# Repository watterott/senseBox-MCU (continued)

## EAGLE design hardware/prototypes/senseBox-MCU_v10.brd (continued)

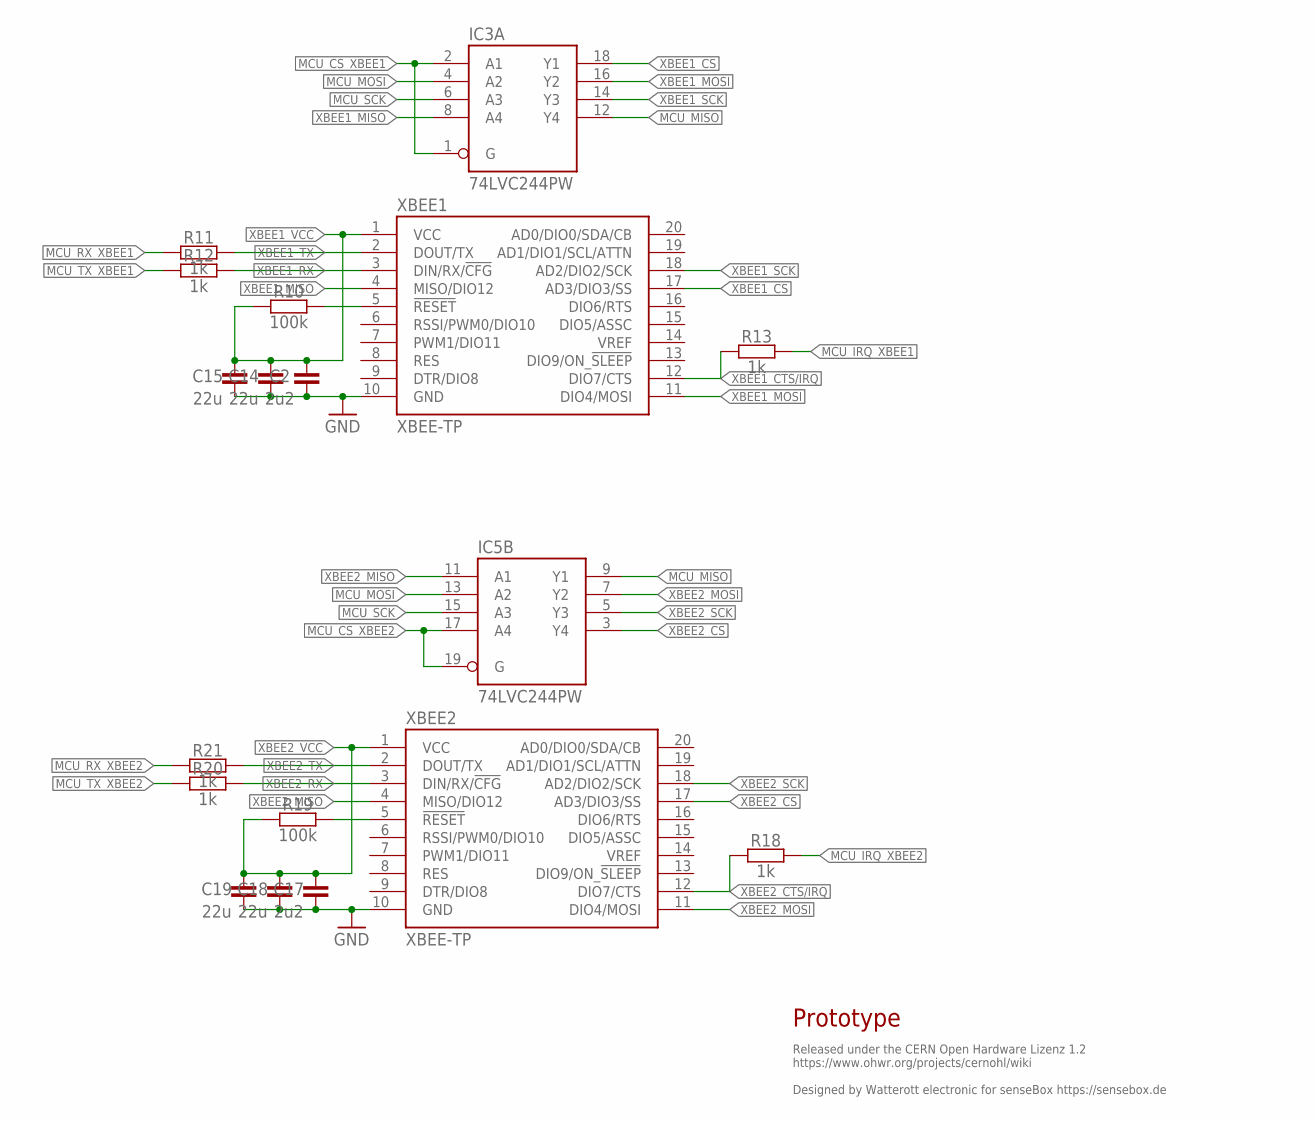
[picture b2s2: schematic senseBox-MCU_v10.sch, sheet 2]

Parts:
C2, C17: 2u2; C0402
C14, C15, C18, C19: 22u; C0805
IC3, IC5: 74LVC244PW; TSSOP20
R10, R19: 100k; C0402
R11, R12, R13, R18, R20, R21: 1k; C0402
XBEE1, XBEE2: XBEE-TP; XBEE_TP

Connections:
GND: C2.1, C14.1, C15.1, C17.1, C18.1, C19.1, XBEE1.10 (GND), XBEE2.10 (GND); also elsewhere on the board
MCU_CS_XBEE1: IC3.1 (G), IC3.2 (A1); also elsewhere on the board
MCU_CS_XBEE2: IC5.17 (A4), IC5.19 (G); also elsewhere on the board
MCU_IRQ_XBEE1: R13.2; also elsewhere on the board
MCU_IRQ_XBEE2: R18.2; also elsewhere on the board
MCU_MISO: IC3.12 (Y4), IC5.9 (Y1); also elsewhere on the board
MCU_MOSI: IC3.4 (A2), IC5.13 (A2); also elsewhere on the board
MCU_RX_XBEE1: R11.1; also elsewhere on the board
MCU_RX_XBEE2: R21.1; also elsewhere on the board
MCU_SCK: IC3.6 (A3), IC5.15 (A3); also elsewhere on the board
MCU_TX_XBEE1: R12.1; also elsewhere on the board
MCU_TX_XBEE2: R20.1; also elsewhere on the board
unnamed: R19.2, XBEE2.5 (!RESET!)
unnamed: R10.2, XBEE1.5 (!RESET!)
XBEE1_CS: IC3.18 (Y1), XBEE1.17 (AD3/DIO3/SS)
XBEE1_CTS/IRQ: R13.1, XBEE1.12 (DIO7/CTS)
XBEE1_MISO: IC3.8 (A4), XBEE1.4 (MISO/DIO12)
XBEE1_MOSI: IC3.16 (Y2), XBEE1.11 (DIO4/MOSI)
XBEE1_RX: R12.2, XBEE1.3 (DIN/RX/!CFG!)
XBEE1_SCK: IC3.14 (Y3), XBEE1.18 (AD2/DIO2/SCK)
XBEE1_TX: R11.2, XBEE1.2 (DOUT/TX)
XBEE1_VCC: C2.2, C14.2, C15.2, R10.1, XBEE1.1 (VCC); also elsewhere on the board
XBEE2_CS: IC5.3 (Y4), XBEE2.17 (AD3/DIO3/SS)
XBEE2_CTS/IRQ: R18.1, XBEE2.12 (DIO7/CTS)
XBEE2_MISO: IC5.11 (A1), XBEE2.4 (MISO/DIO12)
XBEE2_MOSI: IC5.7 (Y2), XBEE2.11 (DIO4/MOSI)
XBEE2_RX: R20.2, XBEE2.3 (DIN/RX/!CFG!)
XBEE2_SCK: IC5.5 (Y3), XBEE2.18 (AD2/DIO2/SCK)
XBEE2_TX: R21.2, XBEE2.2 (DOUT/TX)
XBEE2_VCC: C17.2, C18.2, C19.2, R19.1, XBEE2.1 (VCC); also elsewhere on the board

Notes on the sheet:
Released under the CERN Open Hardware Lizenz 1.2 https://www.ohwr.org/projects/cernohl/wiki Designed by Watterott electronic for senseBox https://sensebox.de
Prototype

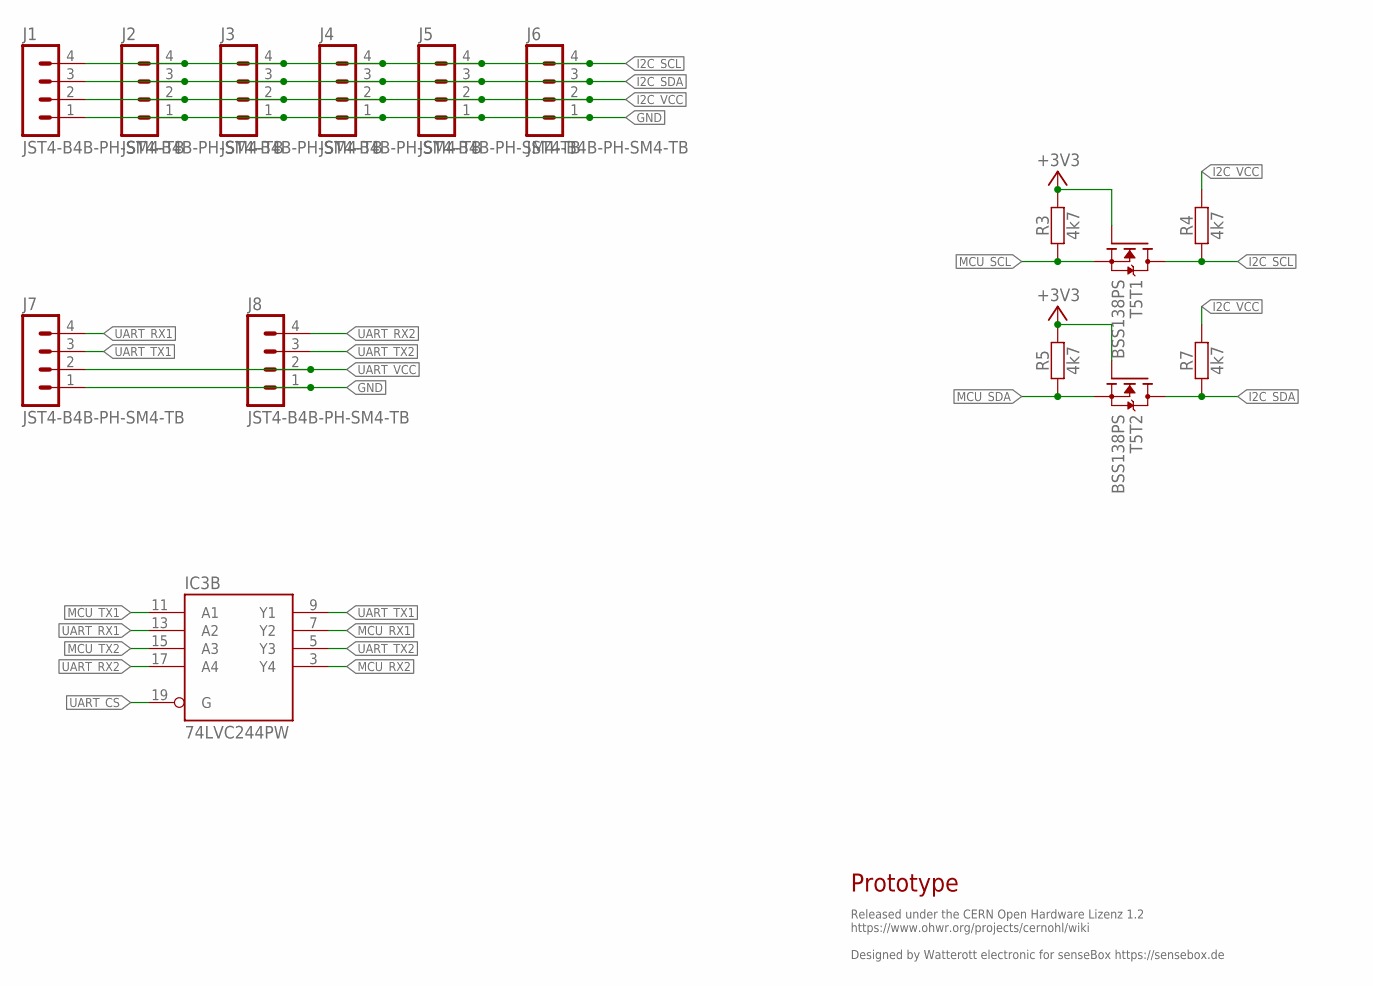
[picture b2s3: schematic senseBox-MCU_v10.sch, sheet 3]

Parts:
IC3: 74LVC244PW; TSSOP20
J1, J2, J3, J4, J5, J6, J7, J8: JST4-B4B-PH-SM4-TB; JST_B4B-PH-SM4-TB
R3, R4, R5, R7: 4k7; C0402
T5: BSS138PS; SOT363

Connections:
+3V3: R3.2, R5.2, T5.2 (G), T5.5 (G); also elsewhere on the board
GND: J1.1, J2.1, J3.1, J4.1, J5.1, J6.1, J7.1, J8.1; also elsewhere on the board
I2C_SCL: J1.4, J2.4, J3.4, J4.4, J5.4, J6.4, R4.1, T5.6 (D)
I2C_SDA: J1.3, J2.3, J3.3, J4.3, J5.3, J6.3, R7.1, T5.3 (D)
I2C_VCC: J1.2, J2.2, J3.2, J4.2, J5.2, J6.2, R4.2, R7.2; also elsewhere on the board
MCU_RX1: IC3.7 (Y2); also elsewhere on the board
MCU_RX2: IC3.3 (Y4); also elsewhere on the board
MCU_SCL: R3.1, T5.1 (S); also elsewhere on the board
MCU_SDA: R5.1, T5.4 (S); also elsewhere on the board
MCU_TX1: IC3.11 (A1); also elsewhere on the board
MCU_TX2: IC3.15 (A3); also elsewhere on the board
UART_CS: IC3.19 (G); also elsewhere on the board
UART_RX1: IC3.13 (A2), J7.4
UART_RX2: IC3.17 (A4), J8.4
UART_TX1: IC3.9 (Y1), J7.3
UART_TX2: IC3.5 (Y3), J8.3
UART_VCC: J7.2, J8.2; also elsewhere on the board

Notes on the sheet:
Released under the CERN Open Hardware Lizenz 1.2 https://www.ohwr.org/projects/cernohl/wiki Designed by Watterott electronic for senseBox https://sensebox.de
Prototype

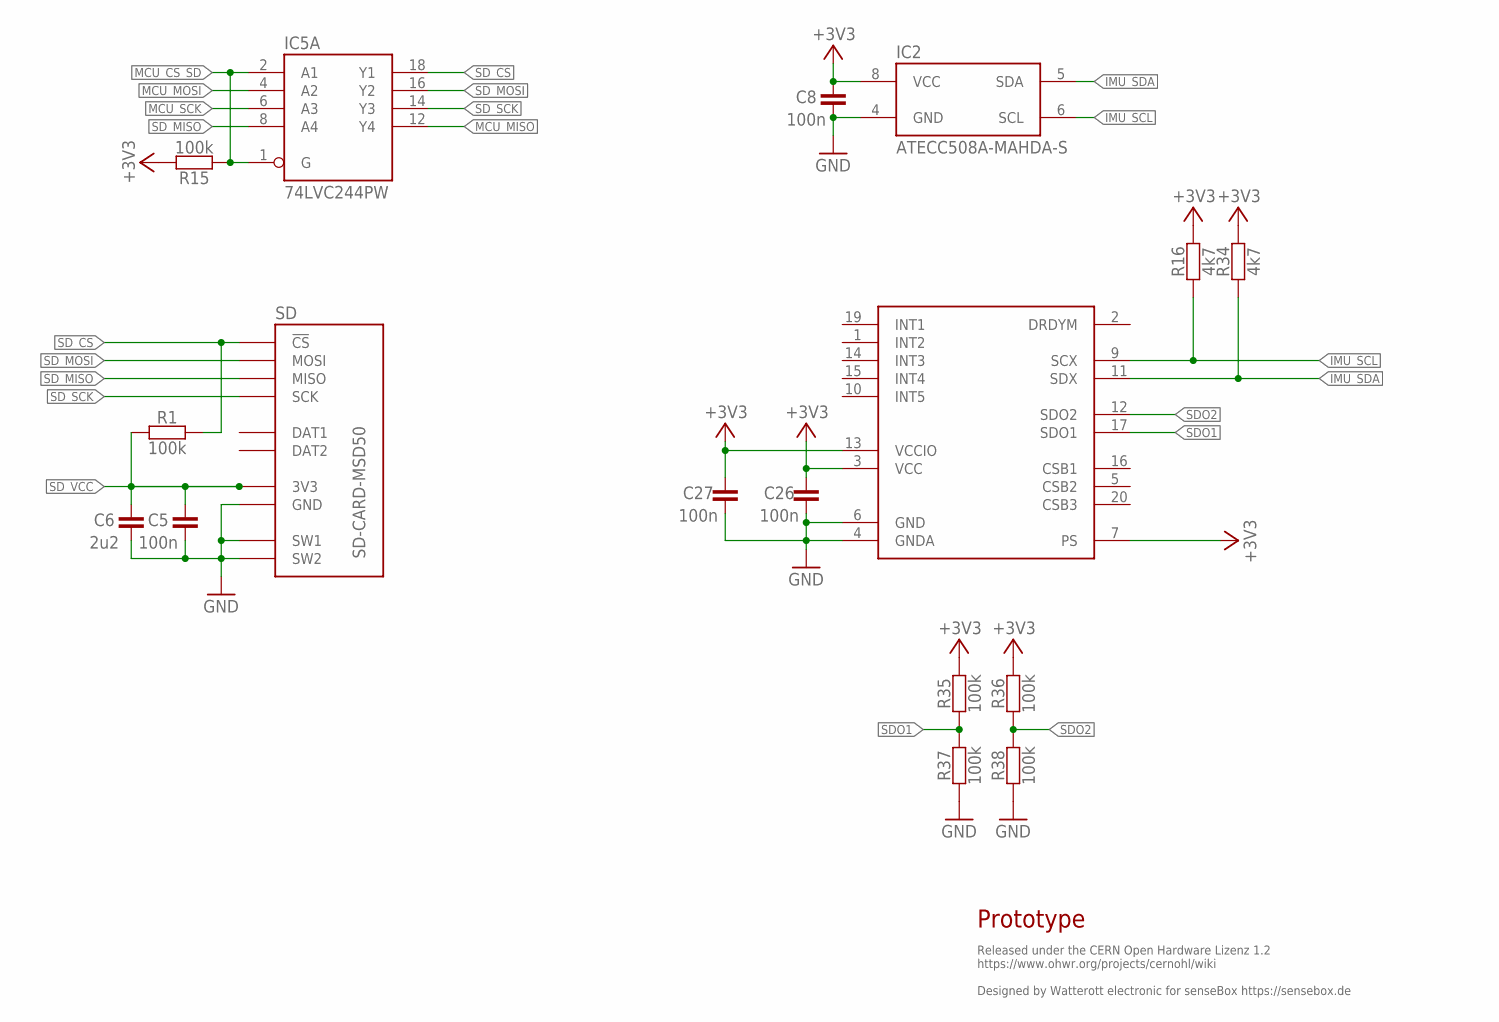
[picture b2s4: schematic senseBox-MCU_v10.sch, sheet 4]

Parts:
C5, C8, C26, C27: 100n; C0402
C6: 2u2; C0402
IC2: ATECC508A-MAHDA-S; UDFN8
IC5: 74LVC244PW; TSSOP20
R1, R15, R35, R36, R37, R38: 100k; C0402
R16, R34: 4k7; C0402
SD: SD-CARD-MSD50; SD_5031821853
U1: BMX055

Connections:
+3V3: C8.2, C26.2, C27.2, IC2.8 (VCC), R15.2, R16.2, R34.2, R35.2, R36.2, U1.3 (VCC), U1.7 (PS), U1.13 (VCCIO); also elsewhere on the board
GND: C5.1, C6.1, C8.1, C26.1, C27.1, IC2.4 (GND), R37.1, R38.1, SD.GND, SD.SW1, SD.SW2, U1.4 (GNDA), U1.6 (GND); also elsewhere on the board
IMU_SCL: IC2.6 (SCL), R16.1, U1.9 (SCX); also elsewhere on the board
IMU_SDA: IC2.5 (SDA), R34.1, U1.11 (SDX); also elsewhere on the board
MCU_CS_SD: IC5.1 (G), IC5.2 (A1), R15.1; also elsewhere on the board
MCU_MISO: IC5.12 (Y4); also elsewhere on the board
MCU_MOSI: IC5.4 (A2); also elsewhere on the board
MCU_SCK: IC5.6 (A3); also elsewhere on the board
SDO1: R35.1, R37.2, U1.17 (SDO1)
SDO2: R36.1, R38.2, U1.12 (SDO2)
SD_CS: IC5.18 (Y1), R1.2, SD.CS (!CS)
SD_MISO: IC5.8 (A4), SD.MISO
SD_MOSI: IC5.16 (Y2), SD.MOSI
SD_SCK: IC5.14 (Y3), SD.SCK
SD_VCC: C5.2, C6.2, R1.1, SD.VCC (3V3); also elsewhere on the board

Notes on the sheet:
Released under the CERN Open Hardware Lizenz 1.2 https://www.ohwr.org/projects/cernohl/wiki Designed by Watterott electronic for senseBox https://sensebox.de
Prototype

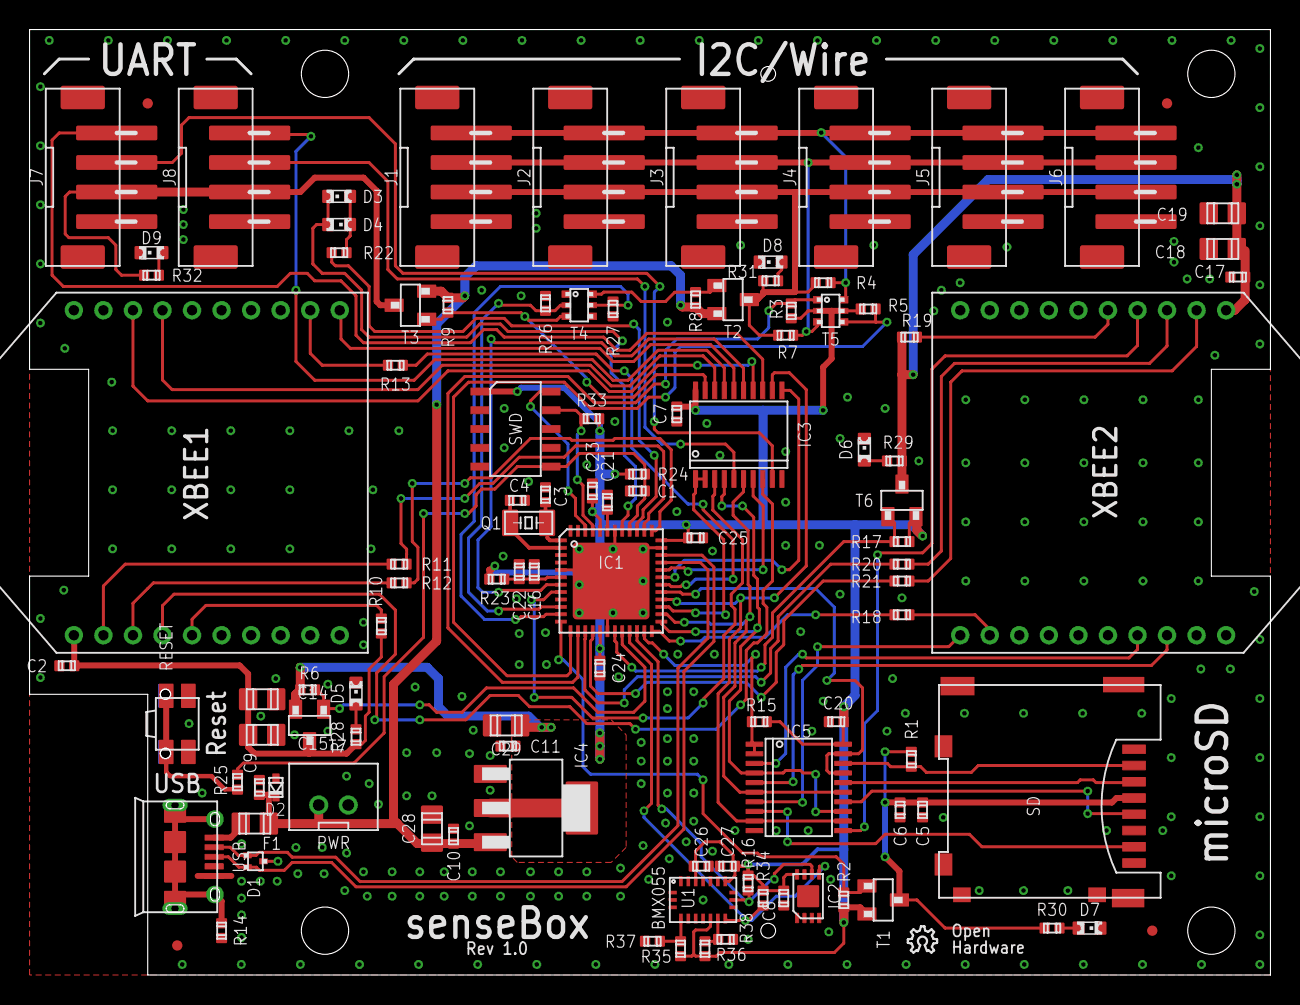
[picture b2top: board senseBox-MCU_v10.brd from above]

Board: 2 copper layers, 84.0 x 64.0 mm, 109 parts (0 on the bottom side), 83 nets.

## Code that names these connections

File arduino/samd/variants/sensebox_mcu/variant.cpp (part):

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 |            |                  |        |                 |   EIC  | ADC |  AC | PTC | DAC | SERCOMx | SERCOMx |  TCCx  |  TCCx  |    COM   | AC/GLCK  |
 |            |                  |        |                 |(EXTINT)|(AIN)|(AIN)|     |     | (x/PAD) | (x/PAD) | (x/WO) | (x/WO) |          |          |
 +------------+------------------+--------+-----------------+--------+-----+-----+-----+-----+---------+---------+--------+--------+----------+----------+
 | 00         | SW               |  PA20  |                 |  *04   |     |     | X08 |     |   5/02  |   3/02  |        |*TCC0/6 | I2S/SCK0 | GCLK_IO4 |
 | 01         | IO1 / REFB       |  PA04  |                 |   04   | *04 |  00 | Y02 |     |         |   0/00  |*TCC0/0 |        |          |          |
 | 02         | IO2              |  PA05  |                 |   05   | *05 |  01 | Y03 |     |         |   0/01  |*TCC0/1 |        |          |          |
 | 03         | IO3              |  PA06  |                 |   06   | *06 |  02 | Y04 |     |         |   0/02  | TCC1/0 |        |          |          |
 | 04         | IO4              |  PA07  |                 |   07   | *07 |  03 | Y05 |     |         |   0/03  | TCC1/1 |        | I2S/SD0  |          |
 | 05         | IO5 / REFA       |  PA03  |                 |   03   |  01 |     | Y01 |     |         |         |        |        |          |          |
 | 06         | IO6 / DAC0       |  PA02  |                 |   02   | *00 |     | Y00 | OUT |         |         |        |        |          |          |
 | 07         | LED red          |  PA27  |                 |   15   |     |     |     |     |         |         |        |        |          | GCLK_IO0 |
 | 08         | LED green        |  PA28  |                 |   08   |     |     |     |     |         |         |        |        |          | GCLK_IO0 |
 +------------+------------------+--------+-----------------+--------+-----+-----+-----+-----+---------+---------+--------+--------+----------+----------+
 */
  { PORTA, 20, PIO_DIGITAL, (PIN_ATTR_DIGITAL                                ), No_ADC_Channel, NOT_ON_PWM, NOT_ON_TIMER, EXTERNAL_INT_4    }, // SW
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 |            |                  |        |                 |   EIC  | ADC |  AC | PTC | DAC | SERCOMx | SERCOMx |  TCCx  |  TCCx  |    COM   | AC/GLCK  |
 |            |                  |        |                 |(EXTINT)|(AIN)|(AIN)|     |     | (x/PAD) | (x/PAD) | (x/WO) | (x/WO) |          |          |
 +------------+------------------+--------+-----------------+--------+-----+-----+-----+-----+---------+---------+--------+--------+----------+----------+
 | 09         | PWR UART         |  PB02  |                 |  *02   | *10 |     | Y08 |     |         |   5/00  |        |        |          |          |
 | 10         | TX1              |  PA22  |                 |  *06   |     |     | X10 |     |   3/00  |   5/00  |* TC4/0 | TCC0/4 |          | GCLK_IO6 |
 | 11         | RX1              |  PA23  |                 |  *07   |     |     | X11 |     |   3/01  |   5/01  |* TC4/1 | TCC0/5 | USB/SOF  | GCLK_IO7 |
 | 12         | TX2              |  PB08  |                 |   08   |  02 |     | Y14 |     |         |   4/00  |  TC4/0 |        |          |          |
 | 13         | RX2              |  PB09  |                 |  *09   |  03 |     | Y15 |     |         |   4/01  |  TC4/1 |        |          |          |
 +------------+------------------+--------+-----------------+--------------------+-----+-----+---------+---------+--------+--------+----------+----------+
 | 14         | PWR I2C          |  PB11  |                 |  *11   |     |     |     |     |         |   4/03  |* TC5/1 | TCC0/5 | I2S/SCK1 | GCLK_IO5 |
 | 15         | SDA              |  PA08  |                 |   NMI  | *16 |     | X00 |     |  *0/00  |   2/00  | TCC0/0 | TCC1/2 | I2S/SD1  |          |
 | 16         | SCL              |  PA09  |                 |   09   | *17 |     | X01 |     |  *0/01  |   2/01  | TCC0/1 | TCC1/3 | I2S/MCK0 |          |
 +------------+------------------+--------+-----------------+--------------------+-----+-----+---------+---------+--------+--------+----------+----------+
 | 17         | SDA IMU          |  PA12  |                 |   12   |     |     |     |     |  *2/00  |   4/00  | TCC2/0 | TCC0/6 |          | AC/CMP0  |
 | 18         | SCL IMU          |  PA13  |                 |   13   |     |     |     |     |  *2/01  |   4/01  | TCC2/1 | TCC0/7 |          | AC/CMP1  |
 +------------+------------------+--------+-----------------+--------------------+-----+-----+---------+---------+--------+--------+----------+----------+
 | 19         | MOSI             |  PA16  |                 |  *00   |     |     | X04 |     |  *1/00  |   3/00  |*TCC2/0 | TCC0/6 |          | GCLK_IO2 |
 | 20         | SCK              |  PA17  |                 |  *01   |     |     | X05 |     |  *1/01  |   3/01  | TCC2/1 | TCC0/7 |          | GCLK_IO3 |
 | 21         | MISO             |  PA19  |                 |   03   |     |     | X07 |     |  *1/03  |   3/03  |* TC3/1 | TCC0/3 | I2S/SD0  | AC/CMP1  |
 +------------+------------------+--------+-----------------+--------------------+-----+-----+---------+---------+--------+--------+----------+----------+
 */
  { PORTB,  2, PIO_DIGITAL, (PIN_ATTR_DIGITAL                                ), No_ADC_Channel, NOT_ON_PWM, NOT_ON_TIMER, EXTERNAL_INT_NONE }, // PWR UART
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 |            |                  |        |                 |   EIC  | ADC |  AC | PTC | DAC | SERCOMx | SERCOMx |  TCCx  |  TCCx  |    COM   | AC/GLCK  |
 |            |                  |        |                 |(EXTINT)|(AIN)|(AIN)|     |     | (x/PAD) | (x/PAD) | (x/WO) | (x/WO) |          |          |
 +------------+------------------+--------+-----------------+--------+-----+-----+-----+-----+---------+---------+--------+--------+----------+----------+
 | 22         | PWR XB1          |  PB03  |                 |  *03   | *11 |     | Y09 |     |         |   5/01  |        |        |          |          |
 | 23         | CS XB1           |  PA18  |                 |   02   |     |     | X06 |     |   1/02  |   3/02  |  TC3/0 | TCC0/2 |          | AC/CMP0  |
 | 24         | INT XB1          |  PA21  |                 |  *05   |     |     | X09 |     |   5/03  |   3/03  |        |*TCC0/7 | I2S/FS0  | GCLK_IO5 |
 | 25         | RX XB1           |  PB23  |                 |   07   |     |     |     |     |         |  *5/03  |        |        |          | GCLK_IO1 |
 | 26         | TX XB1           |  PB22  |                 |   06   |     |     |     |     |         |  *5/02  |        |        |          | GCLK_IO0 |
 +------------+------------------+--------+-----------------+--------------------+-----+-----+---------+---------+--------+--------+----------+----------+
 | 27         | PWR XB2          |  PB10  |                 |  *10   |     |     |     |     |         |   4/02  |* TC5/0 | TCC0/4 | I2S/MCK1 | GCLK_IO4 |
 | 28         | D28 XB2          |  PA14  |                 |   14   |     |     |     |     |   2/02  |   4/02  |  TC3/0 | TCC0/4 |          | GCLK_IO0 |
 | 29         | D29 XB2          |  PA15  |                 |   15   |     |     |     |     |  *2/03  |   4/03  |  TC3/1 | TCC0/5 |          | GCLK_IO1 |
 | 30         | TX XB2           |  PA10  |                 |   10   | *18 |     | X02 |     |   0/02  |   2/02  |*TCC1/0 | TCC0/2 | I2S/SCK0 | GCLK_IO4 |
 | 31         | RX XB2           |  PA11  |                 |   11   | *19 |     | X03 |     |   0/03  |   2/03  |*TCC1/1 | TCC0/3 | I2S/FS0  | GCLK_IO5 |
 +------------+------------------+--------+-----------------+--------+-----+-----+-----+-----+---------+---------+--------+--------+----------+----------+
 */
  { PORTB,  3, PIO_DIGITAL, (PIN_ATTR_DIGITAL                                ), No_ADC_Channel, NOT_ON_PWM, NOT_ON_TIMER, EXTERNAL_INT_NONE }, // PWR XB1
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 |            |                  |        |                 |(EXTINT)|(AIN)|(AIN)|     |     | (x/PAD) | (x/PAD) | (x/WO) | (x/WO) |          |          |
 +------------+------------------+--------+-----------------+--------+-----+-----+-----+-----+---------+---------+--------+--------+----------+----------+
 |            |       USB        |        |                 |        |     |     |     |     |         |         |        |        |          |          |
 | 32         |                  |  PA24  | USB N           |   12   |     |     |     |     |   3/02  |   5/02  |  TC5/0 | TCC1/2 | USB/DM   |          |
 | 33         |                  |  PA25  | USB P           |   13   |     |     |     |     |   3/03  |   5/03  |  TC5/1 | TCC1/3 | USB/DP   |          |
 +------------+------------------+--------+-----------------+--------+-----+-----+-----+-----+---------+---------+--------+--------+----------+----------+
 |            | 32768Hz Crystal  |        |                 |        |     |     |     |     |         |         |        |        |          |          |
 | 34         |                  |  PA00  | XIN32           |   00   |     |     |     |     |         |   1/00  | TCC2/0 |        |          |          |
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
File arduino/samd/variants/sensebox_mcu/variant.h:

/*
  Copyright (c) 2014-2015 Arduino LLC.  All right reserved.

  This library is free software; you can redistribute it and/or
  modify it under the terms of the GNU Lesser General Public
  License as published by the Free Software Foundation; either
  version 2.1 of the License, or (at your option) any later version.

  This library is distributed in the hope that it will be useful,
  but WITHOUT ANY WARRANTY; without even the implied warranty of
  MERCHANTABILITY or FITNESS FOR A PARTICULAR PURPOSE.
  See the GNU Lesser General Public License for more details.

  You should have received a copy of the GNU Lesser General Public
  License along with this library; if not, write to the Free Software
  Foundation, Inc., 51 Franklin St, Fifth Floor, Boston, MA  02110-1301  USA
*/

#pragma once

// The definitions here needs a SAMD core >=1.6.10
#define ARDUINO_SAMD_VARIANT_COMPLIANCE 10610

#include <WVariant.h>

// General definitions
// -------------------

// Frequency of the board main oscillator
#define VARIANT_MAINOSC (32768ul)
//#define CRYSTALLESS //do not use ext. crystal

// Master clock frequency
#define VARIANT_MCK     (48000000ul)

// Pins
// ----

// Number of pins defined in PinDescription array
#define PINS_COUNT           (34u) // 34
#define NUM_DIGITAL_PINS     (32u) // 32
#define NUM_ANALOG_INPUTS    (7u)  // 7
#define NUM_ANALOG_OUTPUTS   (1u)  // 1
#define analogInputToDigitalPin(p)  ((p < 7u) ? (p) : -1)

// Low-level pin register query macros
// -----------------------------------
#define digitalPinToPort(P)      (&(PORT->Group[g_APinDescription[P].ulPort]))
#define digitalPinToBitMask(P)   (1 << g_APinDescription[P].ulPin)
//#define analogInPinToBit(P)    ()
#define portOutputRegister(port) (&(port->OUT.reg))
#define portInputRegister(port)  (&(port->IN.reg))
#define portModeRegister(port)   (&(port->DIR.reg))
#define digitalPinHasPWM(P)      (g_APinDescription[P].ulPWMChannel != NOT_ON_PWM || g_APinDescription[P].ulTCChannel != NOT_ON_TIMER)

/*
 * digitalPinToTimer(..) is AVR-specific and is not defined for SAMD
 * architecture. If you need to check if a pin supports PWM you must
 * use digitalPinHasPWM(..).
 *
 * https://github.com/arduino/Arduino/issues/1833
 */
// #define digitalPinToTimer(P)

// senseBox MCU pins
// -----------------
#define PIN_UART_PWR  (9u)
#define PIN_UART_TX1  (10u)
#define PIN_UART_RX1  (11u)
#define PIN_UART_TX2  (12u)
#define PIN_UART_RX2  (13u)
#define PIN_I2C_PWR   (14u)
#define PIN_XB1_PWR   (22u)
#define PIN_XB1_CS    (23u)
#define PIN_XB1_INT   (24u)
#define PIN_XB1_TX    (25u)
#define PIN_XB1_RX    (26u)
#define PIN_XB2_PWR   (27u)
#define PIN_XB2_CS    (28u)
#define PIN_XB2_INT   (29u)
#define PIN_XB2_TX    (30u)
#define PIN_XB2_RX    (31u)
#define PIN_RED_LED   (7u)
#define PIN_GREEN_LED (8u)
#define PIN_SWITCH    (0u)
#define PIN_IO1       (1u)
#define PIN_IO2       (2u)
#define PIN_IO3       (3u)
#define PIN_IO4       (4u)
#define PIN_IO5       (5u)
#define PIN_IO6       (6u)

// LEDs
// ----
#define PIN_LED      (7u) // D7/PA27 (red)
#define PIN_LED2     (8u) // D8/PA28 (green)
#define LED_BUILTIN  PIN_LED
#define LED_BUILTIN2 PIN_LED2

// Analog pins
// -----------
#define PIN_A0   (1u)
#define PIN_A1   (1u)
#define PIN_A2   (2u)
#define PIN_A3   (3u)
#define PIN_A4   (4u)
#define PIN_A5   (5u)
#define PIN_A6   (6u)
#define PIN_DAC0 (6u)

static const uint8_t A0   = PIN_A0;
static const uint8_t A1   = PIN_A1;
static const uint8_t A2   = PIN_A2;
static const uint8_t A3   = PIN_A3;
static const uint8_t A4   = PIN_A4;
static const uint8_t A5   = PIN_A5;
static const uint8_t A6   = PIN_A6;
static const uint8_t DAC0 = PIN_DAC0;
#define ADC_RESOLUTION 12

// SPI Interfaces
// --------------
#define SPI_INTERFACES_COUNT 1

// SPI
#define PIN_SPI_MISO  (21u)
#define PIN_SPI_MOSI  (19u)
#define PIN_SPI_SCK   (20u)
#define PIN_SPI_SS    (23u) // CS XB1
#define PERIPH_SPI    sercom1 // sercom1 or sercom3
#define PAD_SPI_TX    SPI_PAD_0_SCK_1
#define PAD_SPI_RX    SERCOM_RX_PAD_3
static const uint8_t SS   = PIN_SPI_SS;   // SPI Slave SS not used. Set here only for reference.
static const uint8_t MOSI = PIN_SPI_MOSI;
static const uint8_t MISO = PIN_SPI_MISO;
static const uint8_t SCK  = PIN_SPI_SCK;

// Wire Interfaces
// ---------------
#define WIRE_INTERFACES_COUNT 2

// Wire
#define PIN_WIRE_SDA        (15u)
#define PIN_WIRE_SCL        (16u)
#define PERIPH_WIRE         sercom0 // sercom0 or sercom2
#define WIRE_IT_HANDLER     SERCOM0_Handler
static const uint8_t SDA = PIN_WIRE_SDA;
static const uint8_t SCL = PIN_WIRE_SCL;

#define PIN_WIRE1_SDA       (17u) // IMU
#define PIN_WIRE1_SCL       (18u) // IMU
#define PERIPH_WIRE1        sercom2 // sercom2 or sercom4
#define WIRE1_IT_HANDLER    SERCOM2_Handler
static const uint8_t SDA1 = PIN_WIRE1_SDA;
static const uint8_t SCL1 = PIN_WIRE1_SCL;

// USB
// ---
#define PIN_USB_DM          (32u)
#define PIN_USB_DP          (33u)
//#define PIN_USB_HOST_ENABLE (-1u)

// Needed for WINC1501B (WiFi101) library
// --------------------------------------
#define WINC1501_RESET_PIN   (-1) // no reset pin
#define WINC1501_CHIP_EN_PIN (-1) // no enable pin
#define WINC1501_INTN_PIN    (24) // 24 = INT XB1, 29 = INT XB2
#define WINC1501_SPI         SPI
#define WINC1501_SPI_CS_PIN  (23) // 23 = CS XB1, 28 = CS XB2
//#define NO_HW_CHIP_EN        (1) // No Chip Enable Pin

// Needed for SD library
// ---------------------
#define SDCARD_SS_PIN       (28u) // CS XB2

// Serial ports
// ------------
#ifdef __cplusplus
#include "SERCOM.h"
#include "Uart.h"

// Instances of SERCOM
extern SERCOM sercom0;
extern SERCOM sercom1;
extern SERCOM sercom2;
extern SERCOM sercom3;
extern SERCOM sercom4;
extern SERCOM sercom5;

// SERCOM3 oder SERCOM5 Serial1 UART RXTX1
extern Uart Serial1;
#define PIN_SERIAL1_RX (11u)
#define PIN_SERIAL1_TX (10u)
#define PAD_SERIAL1_TX (UART_TX_PAD_0)
#define PAD_SERIAL1_RX (SERCOM_RX_PAD_1)

// SERCOM4 Serial2 UART RXTX2
extern Uart Serial2;
#define PIN_SERIAL2_RX (13u)
#define PIN_SERIAL2_TX (12u)
#define PAD_SERIAL2_TX (UART_TX_PAD_0)
#define PAD_SERIAL2_RX (SERCOM_RX_PAD_1)

// SERCOM5 Serial3 XBEE1
extern Uart Serial3;
#define PIN_SERIAL3_RX (26u)
#define PIN_SERIAL3_TX (25u)
#define PAD_SERIAL3_TX (UART_TX_PAD_2)
#define PAD_SERIAL3_RX (SERCOM_RX_PAD_3)

// SERCOM0 oder SERCOM2 Serial4 XBEE2
/*
extern Uart Serial4;
#define PIN_SERIAL4_RX (31u)
#define PIN_SERIAL4_TX (30u)
#define PAD_SERIAL4_TX (UART_TX_PAD_2)
#define PAD_SERIAL4_RX (SERCOM_RX_PAD_3)
*/

#endif // __cplusplus

#ifdef __cplusplus
extern "C" {
#endif
unsigned int PINCOUNT_fn();
#ifdef __cplusplus
}
#endif

// These serial port names are intended to allow libraries and architecture-neutral
// sketches to automatically default to the correct port name for a particular type
// of use.  For example, a GPS module would normally connect to SERIAL_PORT_HARDWARE_OPEN,
// the first hardware serial port whose RX/TX pins are not dedicated to another use.
//
// SERIAL_PORT_MONITOR        Port which normally prints to the Arduino Serial Monitor
//
// SERIAL_PORT_USBVIRTUAL     Port which is USB virtual serial
//
// SERIAL_PORT_LINUXBRIDGE    Port which connects to a Linux system via Bridge library
//
// SERIAL_PORT_HARDWARE       Hardware serial port, physical RX & TX pins.
//
// SERIAL_PORT_HARDWARE_OPEN  Hardware serial ports which are open for use.  Their RX & TX
//                            pins are NOT connected to anything by default.
#define SERIAL_PORT_USBVIRTUAL      SerialUSB
#define SERIAL_PORT_MONITOR         SerialUSB
#define SERIAL_PORT_HARDWARE        Serial1
#define SERIAL_PORT_HARDWARE_OPEN   Serial1

// Alias Serial to SerialUSB
#define Serial                      SerialUSB

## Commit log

2017-12-23 added readme
2017-12-23 added Arduino BSP
2017-12-24 updated exmples
2017-12-24 updated pin defines
2017-12-24 updated examples
2018-01-20 updated bootloader
2018-01-20 power on all sockets
2018-02-01 updated WiFi lib
2018-02-01 added microSD example
2018-02-01 updated libs + examples
2018-02-01 updated bsp
2018-02-01 typo fix
2018-02-24 updated name
2018-03-02 updated driver
2018-03-03 renamed file
2018-03-06 updated naming
2018-03-06 changed SERCOM assignment
2018-03-08 renamed files
2018-03-18 updated libs
2018-04-30 update status LED
2018-05-01 updated pin mapping
2018-05-01 updated analog pin map
2018-05-03 added layout and schematics
2018-05-04 updated schematics
2018-05-04 default power state changeable
2018-05-04 deactivate XB on power off
2018-05-28 add example containing complete component test for home setup
2018-06-11 added image
2018-06-26 added sensor mount
2018-07-04 updated SSD1306 init
2018-07-07 updated example
2018-07-08 added HDC1000 lib
2018-07-28 enable pull-up on interrupt pins
2018-07-28 fix lux calculation
2018-07-29 updated ethernet library
2018-08-15 added Arduino BearSSL + ECCX08 lib
2018-08-16 added gerber files
2018-08-16 updated lib
2018-08-31 added prototypes
2018-09-07 updated pin functions
2018-09-13 updated info
2019-01-08 renamed examples
2019-02-03 added rev 1.3
2020-04-15 updated pins
2020-11-04 update ECC608 naming
2021-01-08 power on/off fix
2021-01-13 fix warning
2021-04-07 added rev 1.5
2021-04-21 added SSD1306 example
2023-06-06 senseBox MCU mini
    added senseBox MCU mini
2023-06-06 added Layout
2024-07-05 update example
